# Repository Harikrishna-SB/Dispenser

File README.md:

# Dispenser
soap dispenser without a micro controller

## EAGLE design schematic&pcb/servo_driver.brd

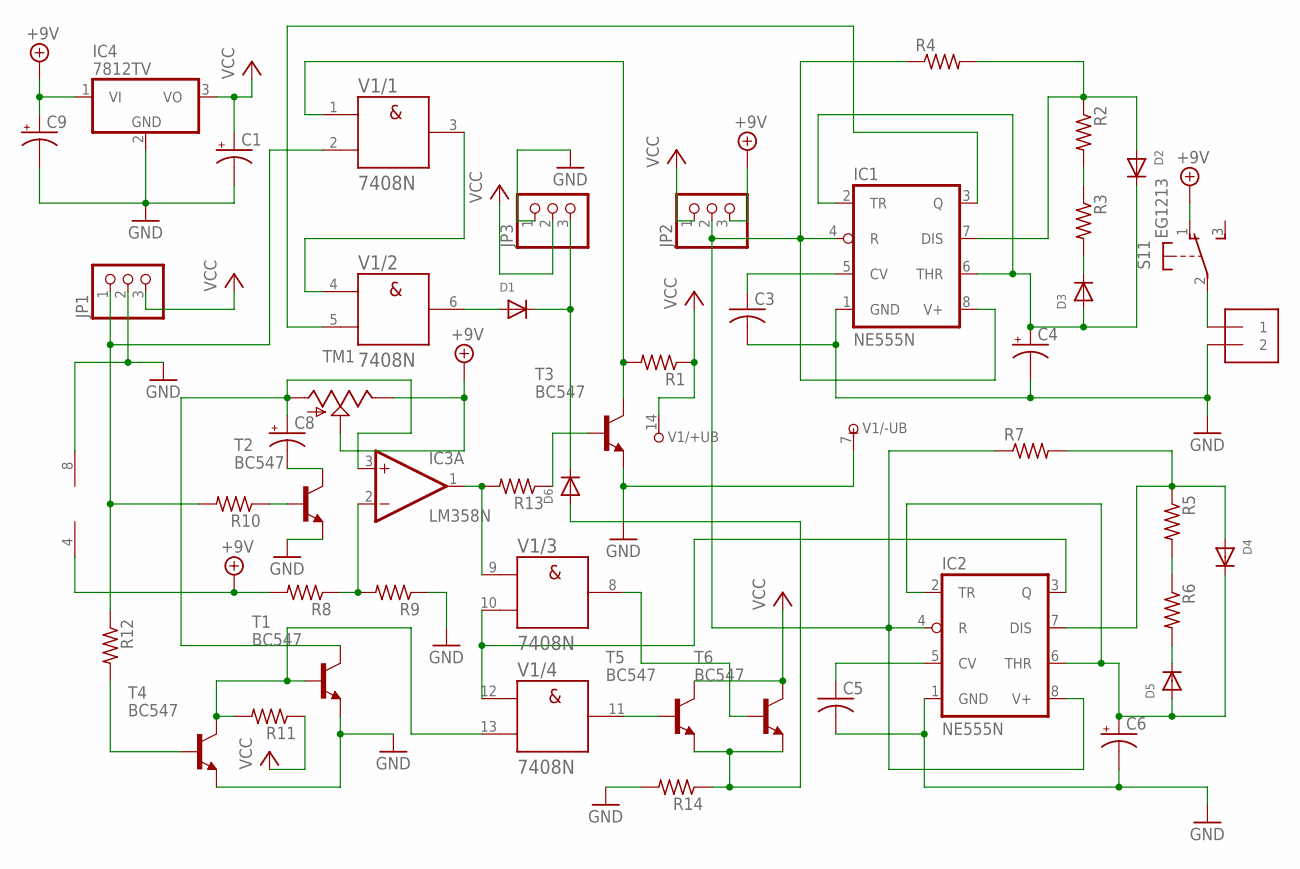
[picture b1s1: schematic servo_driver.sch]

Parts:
C1, C4, C6: CPOL-USE2-4; E2-4
C3, C5: C-US025-030X050; C025-030X050
C8, C9: CPOL-USE2.5-6; E2,5-6
D1, D2, D3, D4, D5, D6: DIODEDO-1N4148; DO-1N4148
IC1, IC2: NE555N; DIL08-ROUND
IC3: LM358N; DIL08
IC4: 7812TV; TO220V
J1: 1X2-3.5MM
JP1, JP2, JP3: PINHD-1X3; 1X03
R1, R2, R3, R4, R5, R6, R7, R8, R9, R10, R11, R12, R13, R14: R-US_0207/9; 0207/9
S1: EG1213
T1, T2, T3, T4, T5, T6: BC547; TO92
TM1: TRIM; 6MM
V1: 7408N; DIL14

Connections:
+9V: C9.+, IC3.4 (V-), IC4.1 (VI), JP2.3, R8.2, S1.1 (O), TM1.E, TM1.S
GND: C1.-, C3.2, C4.-, C5.2, C6.-, C9.-, IC1.1 (GND), IC2.1 (GND), IC3.8 (V+), IC4.2 (GND), J1.2, JP1.2, JP3.1, R9.1, R14.2, T1.1 (E), T2.1 (E), T3.1 (E), T4.1 (E), V1.7 (-UB)
unnamed: C4.+, D2.C, D3.A, IC1.2 (TR), IC1.6 (THR)
unnamed: V1.3 (Y), V1.4 (A)
unnamed: C3.1, IC1.5 (CV)
unnamed: C6.+, D4.C, D5.A, IC2.2 (TR), IC2.6 (THR)
unnamed: R2.2, R3.1
unnamed: D2.A, IC1.7 (DIS), R2.1, R4.2
unnamed: D3.C, R3.2
unnamed: C8.-, T2.3 (C)
unnamed: C5.1, IC2.5 (CV)
unnamed: R5.2, R6.1
unnamed: D4.A, IC2.7 (DIS), R5.1, R7.2
unnamed: D5.C, R6.2
unnamed: D1.A, V1.6 (Y)
unnamed: D1.C, D6.C, JP3.3
unnamed: R1.2, T3.3 (C), V1.1 (A)
unnamed: R13.1, T3.2 (B)
unnamed: IC3.2 (-IN), R8.1, R9.2
unnamed: D6.A, R14.1, T5.1 (E), T6.1 (E)
unnamed: C8.+, IC3.3 (+IN), T1.3 (C), TM1.A
unnamed: JP1.1, R10.2, R12.1, V1.2 (B)
unnamed: R10.1, T2.2 (B)
unnamed: R11.2, T1.2 (B), T4.3 (C), V1.13 (B)
unnamed: R12.2, T4.2 (B)
unnamed: J1.1, S1.2
unnamed: IC1.4 (R), IC1.8 (V+), IC2.4 (R), IC2.8 (V+), JP2.2, R4.1, R7.1
unnamed: IC1.3 (Q), V1.5 (B)
unnamed: IC3.1 (OUT), R13.2, V1.9 (A)
unnamed: IC2.3 (Q), V1.10 (B), V1.12 (A)
unnamed: T6.2 (B), V1.8 (Y)
unnamed: T5.2 (B), V1.11 (Y)
VCC: C1.+, IC4.3 (VO), JP1.3, JP2.1, JP3.2, R1.1, R11.1, T5.3 (C), T6.3 (C), V1.14 (+UB)

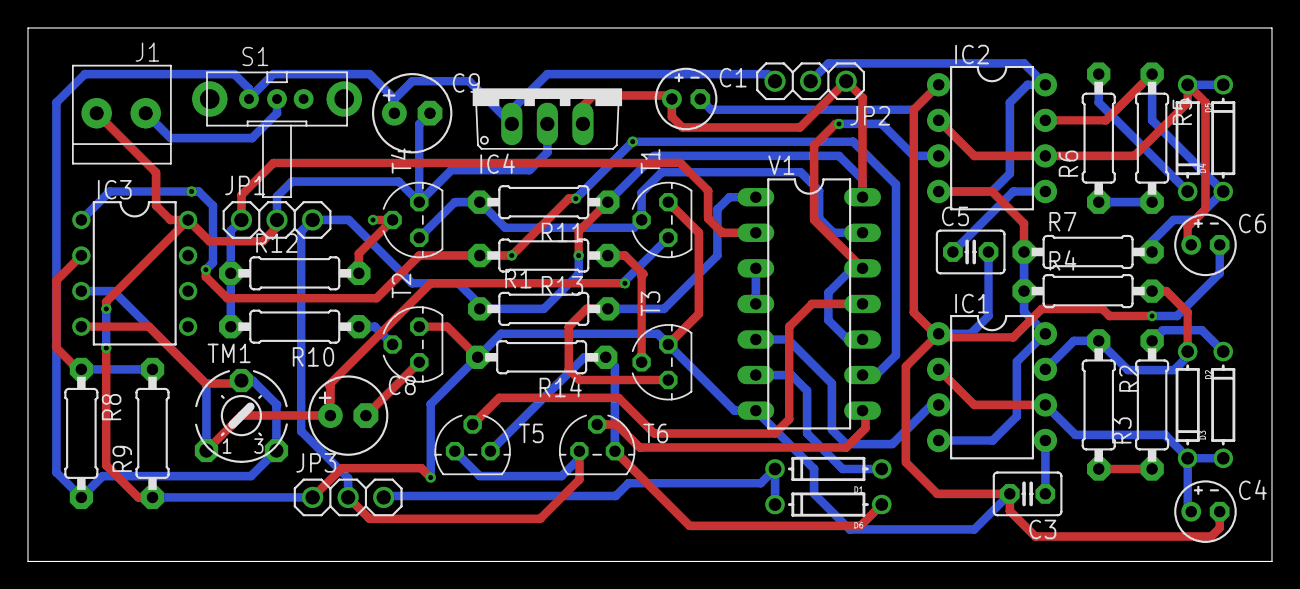
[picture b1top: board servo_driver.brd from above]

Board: 2 copper layers, 88.8 x 38.1 mm, 44 parts (0 on the bottom side), 33 nets.

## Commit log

2020-04-02 schematic and layout added
